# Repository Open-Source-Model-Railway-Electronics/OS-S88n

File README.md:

# OS-S88n-CS

The OS-S88n modules provide feedback functionality for DCC model railroads using the standardized S88n protocol. These modules allow real-time monitoring of block occupancy and layout events by sending data to your command station or PC-based software.

Models:
    • OS-S88n GND — Standard input module using ground-contact detection  
    • OS-S88n CS — current-sensing module  
    • OS-S88n OPTO — Opto-isolated module for clean, noise-free sensor inputs  

All versions include:
    • Daisy-chainable S88n connectors (RJ-45)  
    • Screw terminals for simple input wiring  
    • Compatibility with all major command stations and software (iTrain, Rocrail, Windigipet, etc.)

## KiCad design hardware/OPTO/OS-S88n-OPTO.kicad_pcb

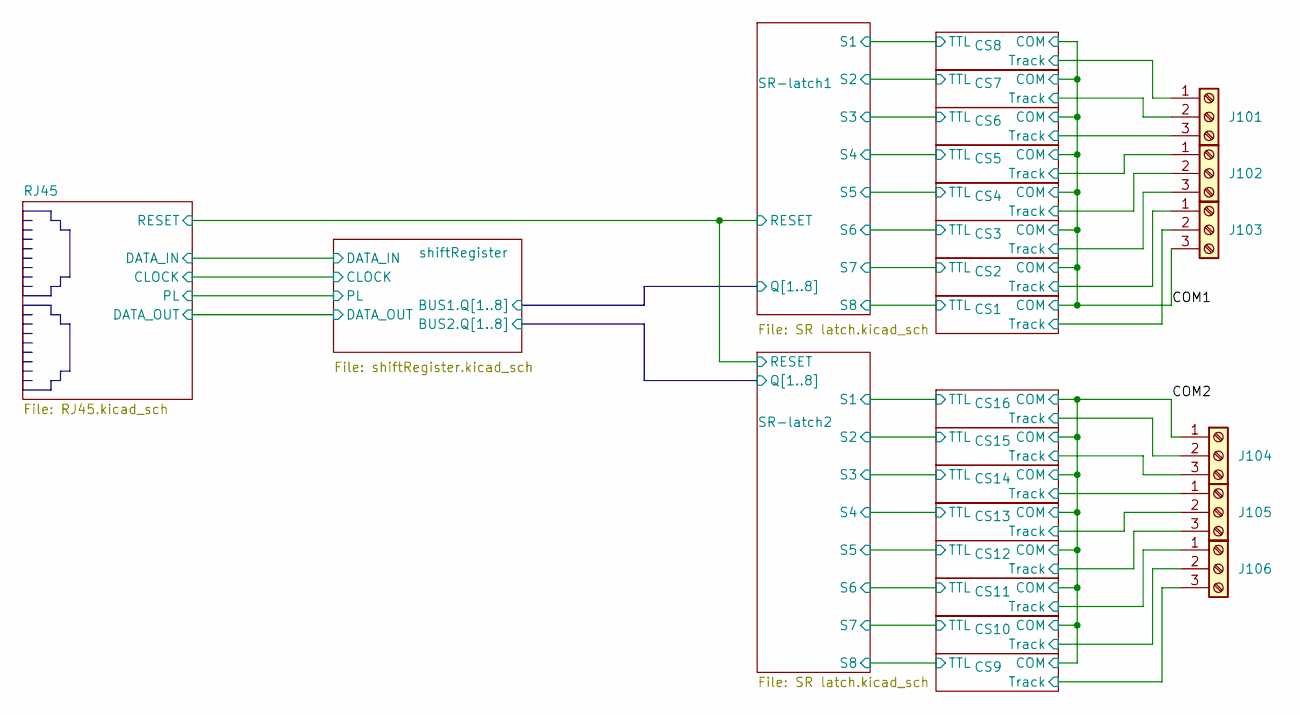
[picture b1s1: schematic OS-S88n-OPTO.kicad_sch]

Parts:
J101, J102, J103, J104, J105, J106: Screw_Terminal_01x03; TerminalBlock_Phoenix_MKDS-1,5-3-5.08_1x03_P5.08mm_Horizont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; JLCPCB Part# C557666

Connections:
/COM1: J103.3; also elsewhere on the board
/COM2: J104.1; also elsewhere on the board
/CS1/Track: J103.2; also elsewhere on the board
/CS2/Track: J103.1; also elsewhere on the board
/CS3/Track: J102.3; also elsewhere on the board
/CS4/Track: J102.2; also elsewhere on the board
/CS5/Track: J102.1; also elsewhere on the board
/CS6/Track: J101.3; also elsewhere on the board
/CS7/Track: J101.2; also elsewhere on the board
/CS8/Track: J101.1; also elsewhere on the board
/CS9/Track: J106.3; also elsewhere on the board
/CS10/Track: J106.2; also elsewhere on the board
/CS11/Track: J106.1; also elsewhere on the board
/CS12/Track: J105.3; also elsewhere on the board
/CS13/Track: J105.2; also elsewhere on the board
/CS14/Track: J105.1; also elsewhere on the board
/CS15/Track: J104.3; also elsewhere on the board
/CS16/Track: J104.2; also elsewhere on the board

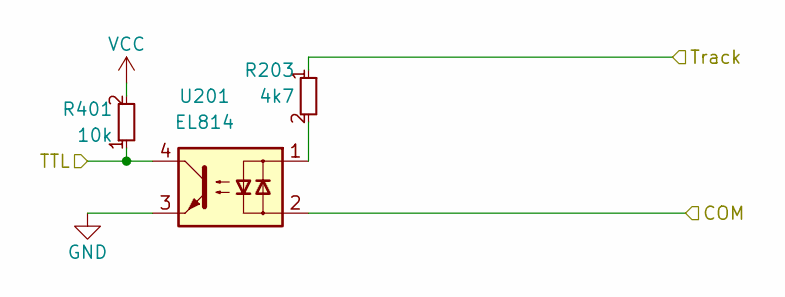
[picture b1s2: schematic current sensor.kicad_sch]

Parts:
R203: 4k7; R_0603_smalltext; JLCPCB Part# C23162
R401: 10k; R_0603_smalltext; JLCPCB Part# C25804
U201: EL814; SMDIP-4_W9.53mm; JLCPCB Part# C500388

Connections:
/COM1: U201.2; also elsewhere on the board
/CS1/Track: R203.1; also elsewhere on the board
unnamed: R203.2, U201.1

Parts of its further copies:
R201, R501, R601, R701, R801, R901, R1001, R1101, R1301, R1401, R1501, R1601, R1701, R1801, R1901: 10k; R_0603_smalltext; JLCPCB Part# C25804
R403, R503, R603, R703, R803, R903, R1003, R1103, R1303, R1403, R1503, R1603, R1703, R1803, R1903: 4k7; R_0603_smalltext; JLCPCB Part# C23162
U401, U501, U601, U701, U801, U901, U1001, U1101, U1301, U1401, U1501, U1601, U1701, U1801, U1901: EL814; SMDIP-4_W9.53mm; JLCPCB Part# C500388

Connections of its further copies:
/COM1: U401.2, U501.2, U601.2, U701.2, U801.2, U901.2, U1001.2; also elsewhere on the board
/COM2: U1101.2, U1301.2, U1401.2, U1501.2, U1601.2, U1701.2, U1801.2, U1901.2; also elsewhere on the board
/CS2/Track: R403.1; also elsewhere on the board
/CS3/TTL: R501.1, U501.4; also elsewhere on the board
/CS3/Track: R503.1; also elsewhere on the board
/CS4/TTL: R601.1, U601.4; also elsewhere on the board
/CS4/Track: R603.1; also elsewhere on the board
/CS5/TTL: R701.1, U701.4; also elsewhere on the board
/CS5/Track: R703.1; also elsewhere on the board
/CS6/TTL: R801.1, U801.4; also elsewhere on the board
/CS6/Track: R803.1; also elsewhere on the board
/CS7/TTL: R901.1, U901.4; also elsewhere on the board
/CS7/Track: R903.1; also elsewhere on the board
/CS8/TTL: R1001.1, U1001.4; also elsewhere on the board
/CS8/Track: R1003.1; also elsewhere on the board
/CS9/TTL: R1101.1, U1101.4; also elsewhere on the board
/CS9/Track: R1103.1; also elsewhere on the board
/CS10/TTL: R1301.1, U1301.4; also elsewhere on the board
/CS10/Track: R1303.1; also elsewhere on the board
/CS11/TTL: R1401.1, U1401.4; also elsewhere on the board
/CS11/Track: R1403.1; also elsewhere on the board
/CS12/TTL: R1501.1, U1501.4; also elsewhere on the board
/CS12/Track: R1503.1; also elsewhere on the board
/CS13/TTL: R1601.1, U1601.4; also elsewhere on the board
/CS13/Track: R1603.1; also elsewhere on the board
/CS14/TTL: R1701.1, U1701.4; also elsewhere on the board
/CS14/Track: R1703.1; also elsewhere on the board
/CS15/TTL: R1801.1, U1801.4; also elsewhere on the board
/CS15/Track: R1803.1; also elsewhere on the board
/CS16/TTL: R1901.1, U1901.4; also elsewhere on the board
/CS16/Track: R1903.1; also elsewhere on the board
unnamed: R403.2, U401.1
unnamed: R503.2, U501.1
unnamed: R603.2, U601.1
unnamed: R703.2, U701.1
unnamed: R803.2, U801.1
unnamed: R903.2, U901.1
unnamed: R1003.2, U1001.1
unnamed: R1103.2, U1101.1
unnamed: R1303.2, U1301.1
unnamed: R1403.2, U1401.1
unnamed: R1503.2, U1501.1
unnamed: R1603.2, U1601.1
unnamed: R1703.2, U1701.1
unnamed: R1803.2, U1801.1
unnamed: R1903.2, U1901.1

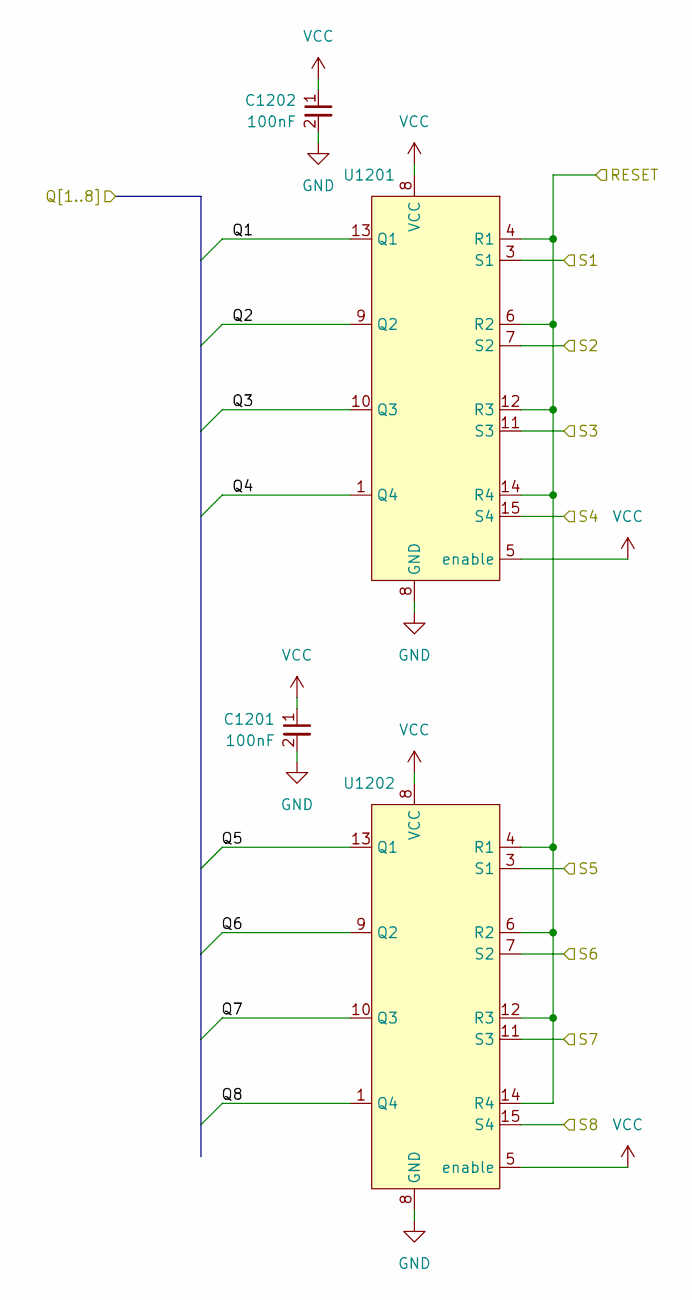
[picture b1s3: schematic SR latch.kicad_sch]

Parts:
C1201, C1202: 100nF; C_0402_1005Metric; JLCPCB Part# C307331
U1201, U1202: SOIC-16_3.9x9.9mm_P1.27mm; JLCPCB Part# C133986

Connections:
/CS9/TTL: U1202.15 (S4); also elsewhere on the board
/CS10/TTL: U1202.11 (S3); also elsewhere on the board
/CS11/TTL: U1202.7 (S2); also elsewhere on the board
/CS12/TTL: U1202.3 (S1); also elsewhere on the board
/CS13/TTL: U1201.15 (S4); also elsewhere on the board
/CS14/TTL: U1201.11 (S3); also elsewhere on the board
/CS15/TTL: U1201.7 (S2); also elsewhere on the board
/CS16/TTL: U1201.3 (S1); also elsewhere on the board
/RJ45/RESET: U1201.4 (R1), U1201.6 (R2), U1201.12 (R3), U1201.14 (R4), U1202.4 (R1), U1202.6 (R2), U1202.12 (R3), U1202.14 (R4); also elsewhere on the board
/SR-latch2/Q1: U1201.13 (Q1); also elsewhere on the board
/SR-latch2/Q2: U1201.9 (Q2); also elsewhere on the board
/SR-latch2/Q3: U1201.10 (Q3); also elsewhere on the board
/SR-latch2/Q4: U1201.1 (Q4); also elsewhere on the board
/SR-latch2/Q5: U1202.13 (Q1); also elsewhere on the board
/SR-latch2/Q6: U1202.9 (Q2); also elsewhere on the board
/SR-latch2/Q7: U1202.10 (Q3); also elsewhere on the board
/SR-latch2/Q8: U1202.1 (Q4); also elsewhere on the board

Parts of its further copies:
C301, C302: 100nF; C_0402_1005Metric; JLCPCB Part# C307331
U301, U302: SOIC-16_3.9x9.9mm_P1.27mm; JLCPCB Part# C133986

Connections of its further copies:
/CS3/TTL: U302.7 (S2); also elsewhere on the board
/CS4/TTL: U302.3 (S1); also elsewhere on the board
/CS5/TTL: U301.15 (S4); also elsewhere on the board
/CS6/TTL: U301.11 (S3); also elsewhere on the board
/CS7/TTL: U301.7 (S2); also elsewhere on the board
/CS8/TTL: U301.3 (S1); also elsewhere on the board
/RJ45/RESET: U301.4 (R1), U301.6 (R2), U301.12 (R3), U301.14 (R4), U302.4 (R1), U302.6 (R2), U302.12 (R3), U302.14 (R4); also elsewhere on the board
/SR-latch1/Q1: U301.13 (Q1); also elsewhere on the board
/SR-latch1/Q2: U301.9 (Q2); also elsewhere on the board
/SR-latch1/Q3: U301.10 (Q3); also elsewhere on the board
/SR-latch1/Q4: U301.1 (Q4); also elsewhere on the board
/SR-latch1/Q5: U302.13 (Q1); also elsewhere on the board
/SR-latch1/Q6: U302.9 (Q2); also elsewhere on the board
/SR-latch1/Q7: U302.10 (Q3); also elsewhere on the board
/SR-latch1/Q8: U302.1 (Q4); also elsewhere on the board

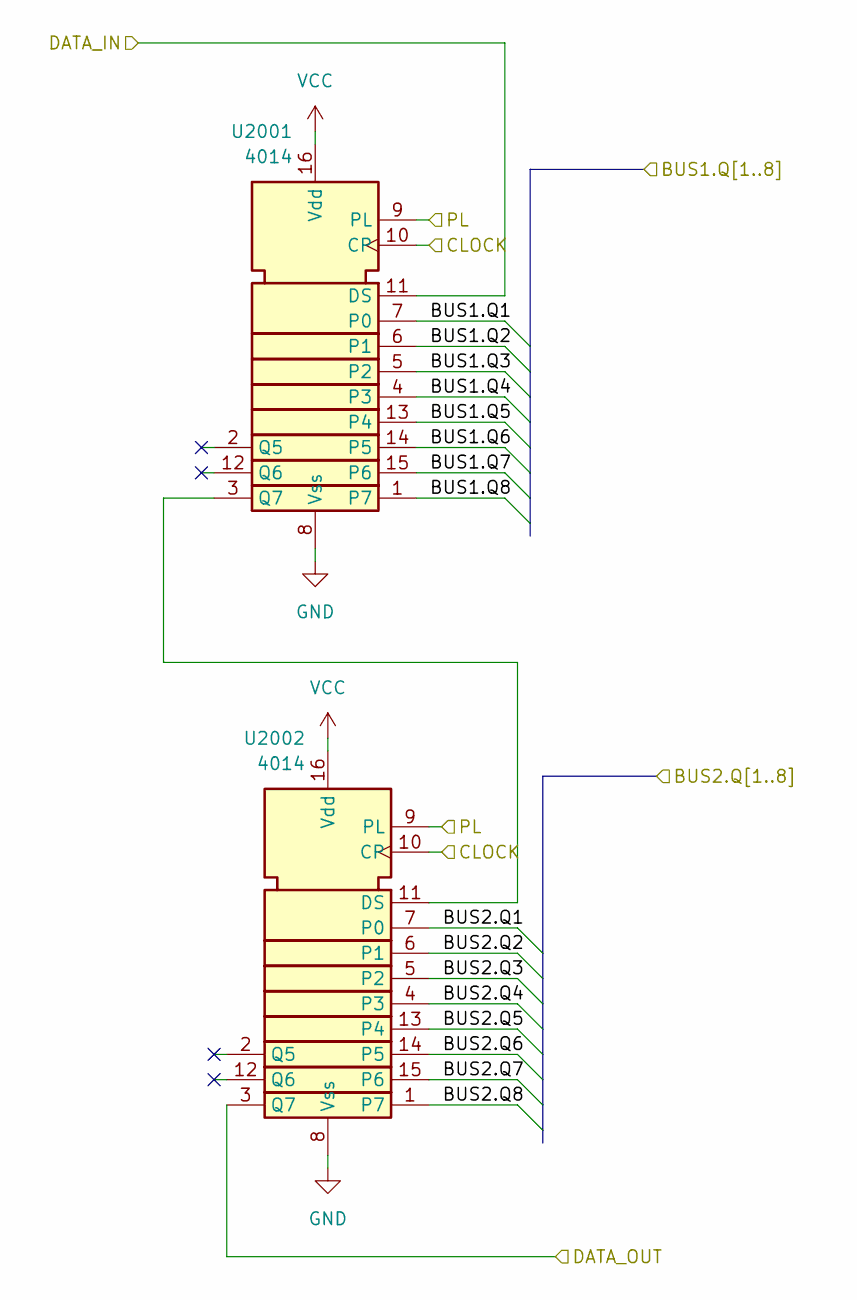
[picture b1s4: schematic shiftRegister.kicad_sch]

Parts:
U2001, U2002: 4014; SOIC-16_3.9x9.9mm_P1.27mm; JLCPCB Part# C496106

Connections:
/RJ45/CLOCK: U2001.10 (CP), U2002.10 (CP); also elsewhere on the board
/RJ45/DATA_IN: U2001.11 (DS); also elsewhere on the board
/RJ45/DATA_OUT: U2002.3 (Q7); also elsewhere on the board
/RJ45/PL: U2001.9 (PL), U2002.9 (PL); also elsewhere on the board
/SR-latch1/Q1: U2001.7 (P0); also elsewhere on the board
/SR-latch1/Q2: U2001.6 (P1); also elsewhere on the board
/SR-latch1/Q3: U2001.5 (P2); also elsewhere on the board
/SR-latch1/Q4: U2001.4 (P3); also elsewhere on the board
/SR-latch1/Q5: U2001.13 (P4); also elsewhere on the board
/SR-latch1/Q6: U2001.14 (P5); also elsewhere on the board
/SR-latch1/Q7: U2001.15 (P6); also elsewhere on the board
/SR-latch1/Q8: U2001.1 (P7); also elsewhere on the board
/SR-latch2/Q1: U2002.7 (P0); also elsewhere on the board
/SR-latch2/Q2: U2002.6 (P1); also elsewhere on the board
/SR-latch2/Q3: U2002.5 (P2); also elsewhere on the board
/SR-latch2/Q4: U2002.4 (P3); also elsewhere on the board
/SR-latch2/Q5: U2002.13 (P4); also elsewhere on the board
/SR-latch2/Q6: U2002.14 (P5); also elsewhere on the board
/SR-latch2/Q7: U2002.15 (P6); also elsewhere on the board
/SR-latch2/Q8: U2002.1 (P7); also elsewhere on the board
unnamed: U2001.3 (Q7), U2002.11 (DS)

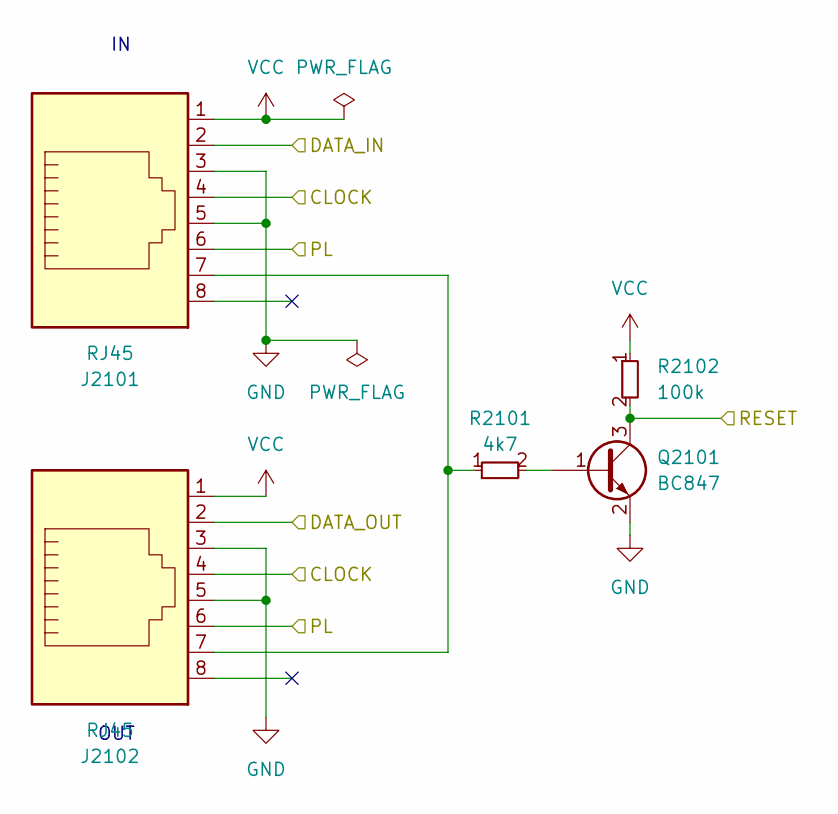
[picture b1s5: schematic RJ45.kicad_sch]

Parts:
J2101, J2102: RJ45; RJ45_Amphenol_54602-x08_Horizontal; JLCPCB Part# C2847314
Q2101: BC847; SOT-23; JLCPCB Part# C181140
R2101: 4k7; R_0603_smalltext; JLCPCB Part# C23162
R2102: 100k; R_0603_smalltext; JLCPCB Part# C25803

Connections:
/RJ45/CLOCK: J2101.4, J2102.4; also elsewhere on the board
/RJ45/DATA_IN: J2101.2; also elsewhere on the board
/RJ45/DATA_OUT: J2102.2; also elsewhere on the board
/RJ45/PL: J2101.6, J2102.6; also elsewhere on the board
/RJ45/RESET: Q2101.3 (C), R2102.2; also elsewhere on the board
unnamed: J2101.7, J2102.7, R2101.1
unnamed: Q2101.1 (B), R2101.2

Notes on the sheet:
OUT

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
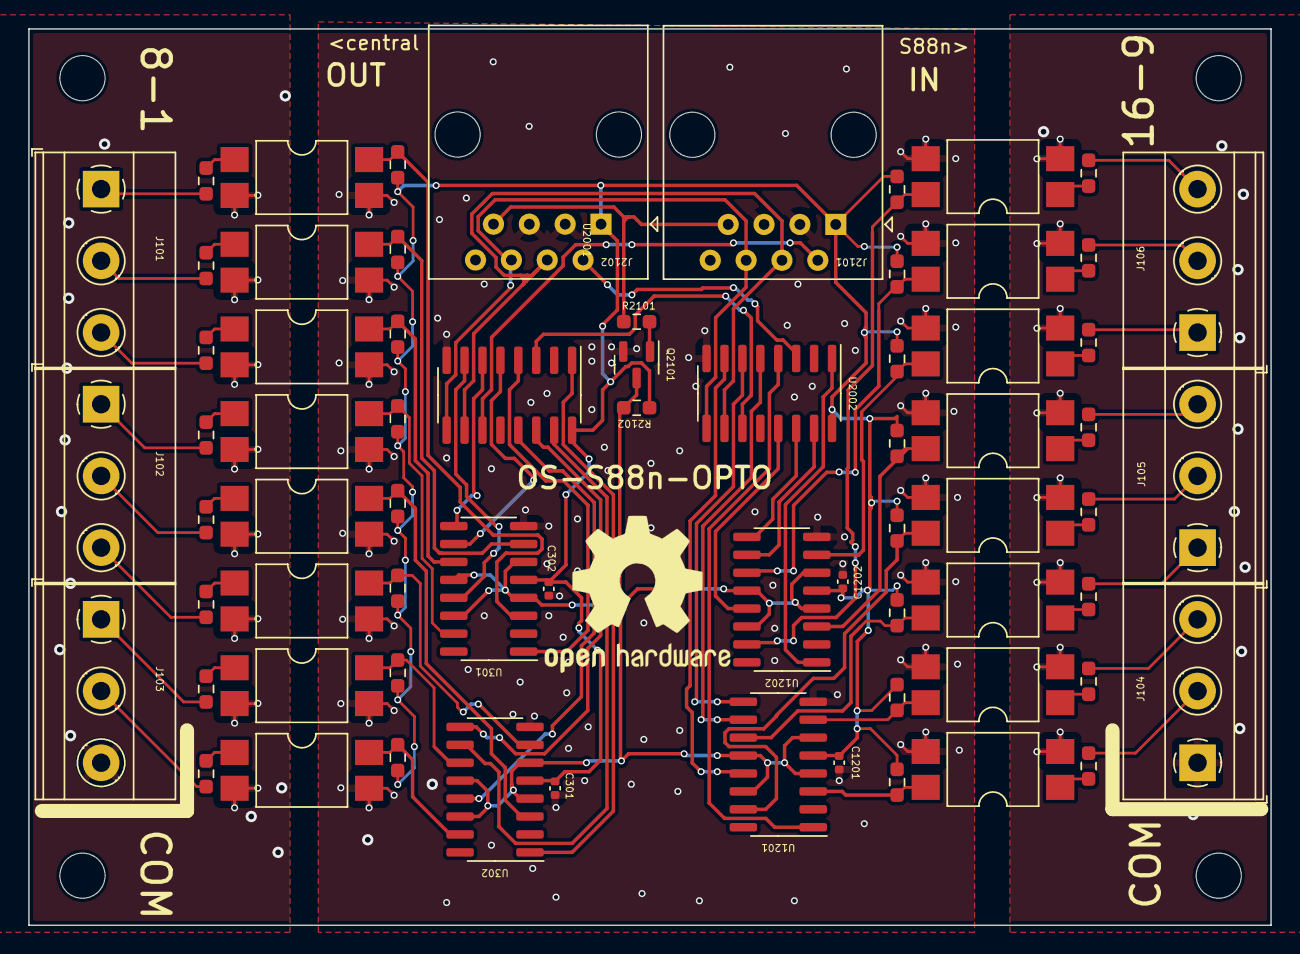
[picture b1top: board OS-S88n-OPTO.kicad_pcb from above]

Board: 2 copper layers, 88.0 x 63.5 mm, 69 parts (0 on the bottom side), 76 nets.

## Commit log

2025-11-13 Major overhaul, added the OS-S88n-OPTO, reorganized release files and documentation
2025-11-13 added all.png
2025-11-15 upadted readme
2026-05-24 added translations
2026-05-25 added pic
